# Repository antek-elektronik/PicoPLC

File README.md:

# picoPLC

Work in progress! 

This is 'industriual' adaptation for raspberry pi pico 2W. This is a hobby project developed by me (AntekElektronik) with no plans for building it (yet). 

## features 

This device features a 8 optotransistor 24V inputs, 4 10A 230V relay outputs and 4 transistor outputs latching to ground. The device is powered by 24V external power supply and has 24V -> 5V switching power regulator onboard (the rpi pico 2w takes care of regulating 3.3V). 

## wireles connectivity

I am aware that rpi pico's wireless features won't work enclosed inside a metal case. I plan on changing to esp32 with external antenna in future. This project could be used as a base for mainstream microcontroller based PLC controllers

## software

for the time of writing this, I do not have any software written. First stage would be a micropython file with predefined variables and functions for basic I/O operations on picoPLC platform, the rest would have to be written in micropython. 

I plan to use an existng project like openPLC, find something similar or write from scratch a program for executing ladder logic or function blocks.

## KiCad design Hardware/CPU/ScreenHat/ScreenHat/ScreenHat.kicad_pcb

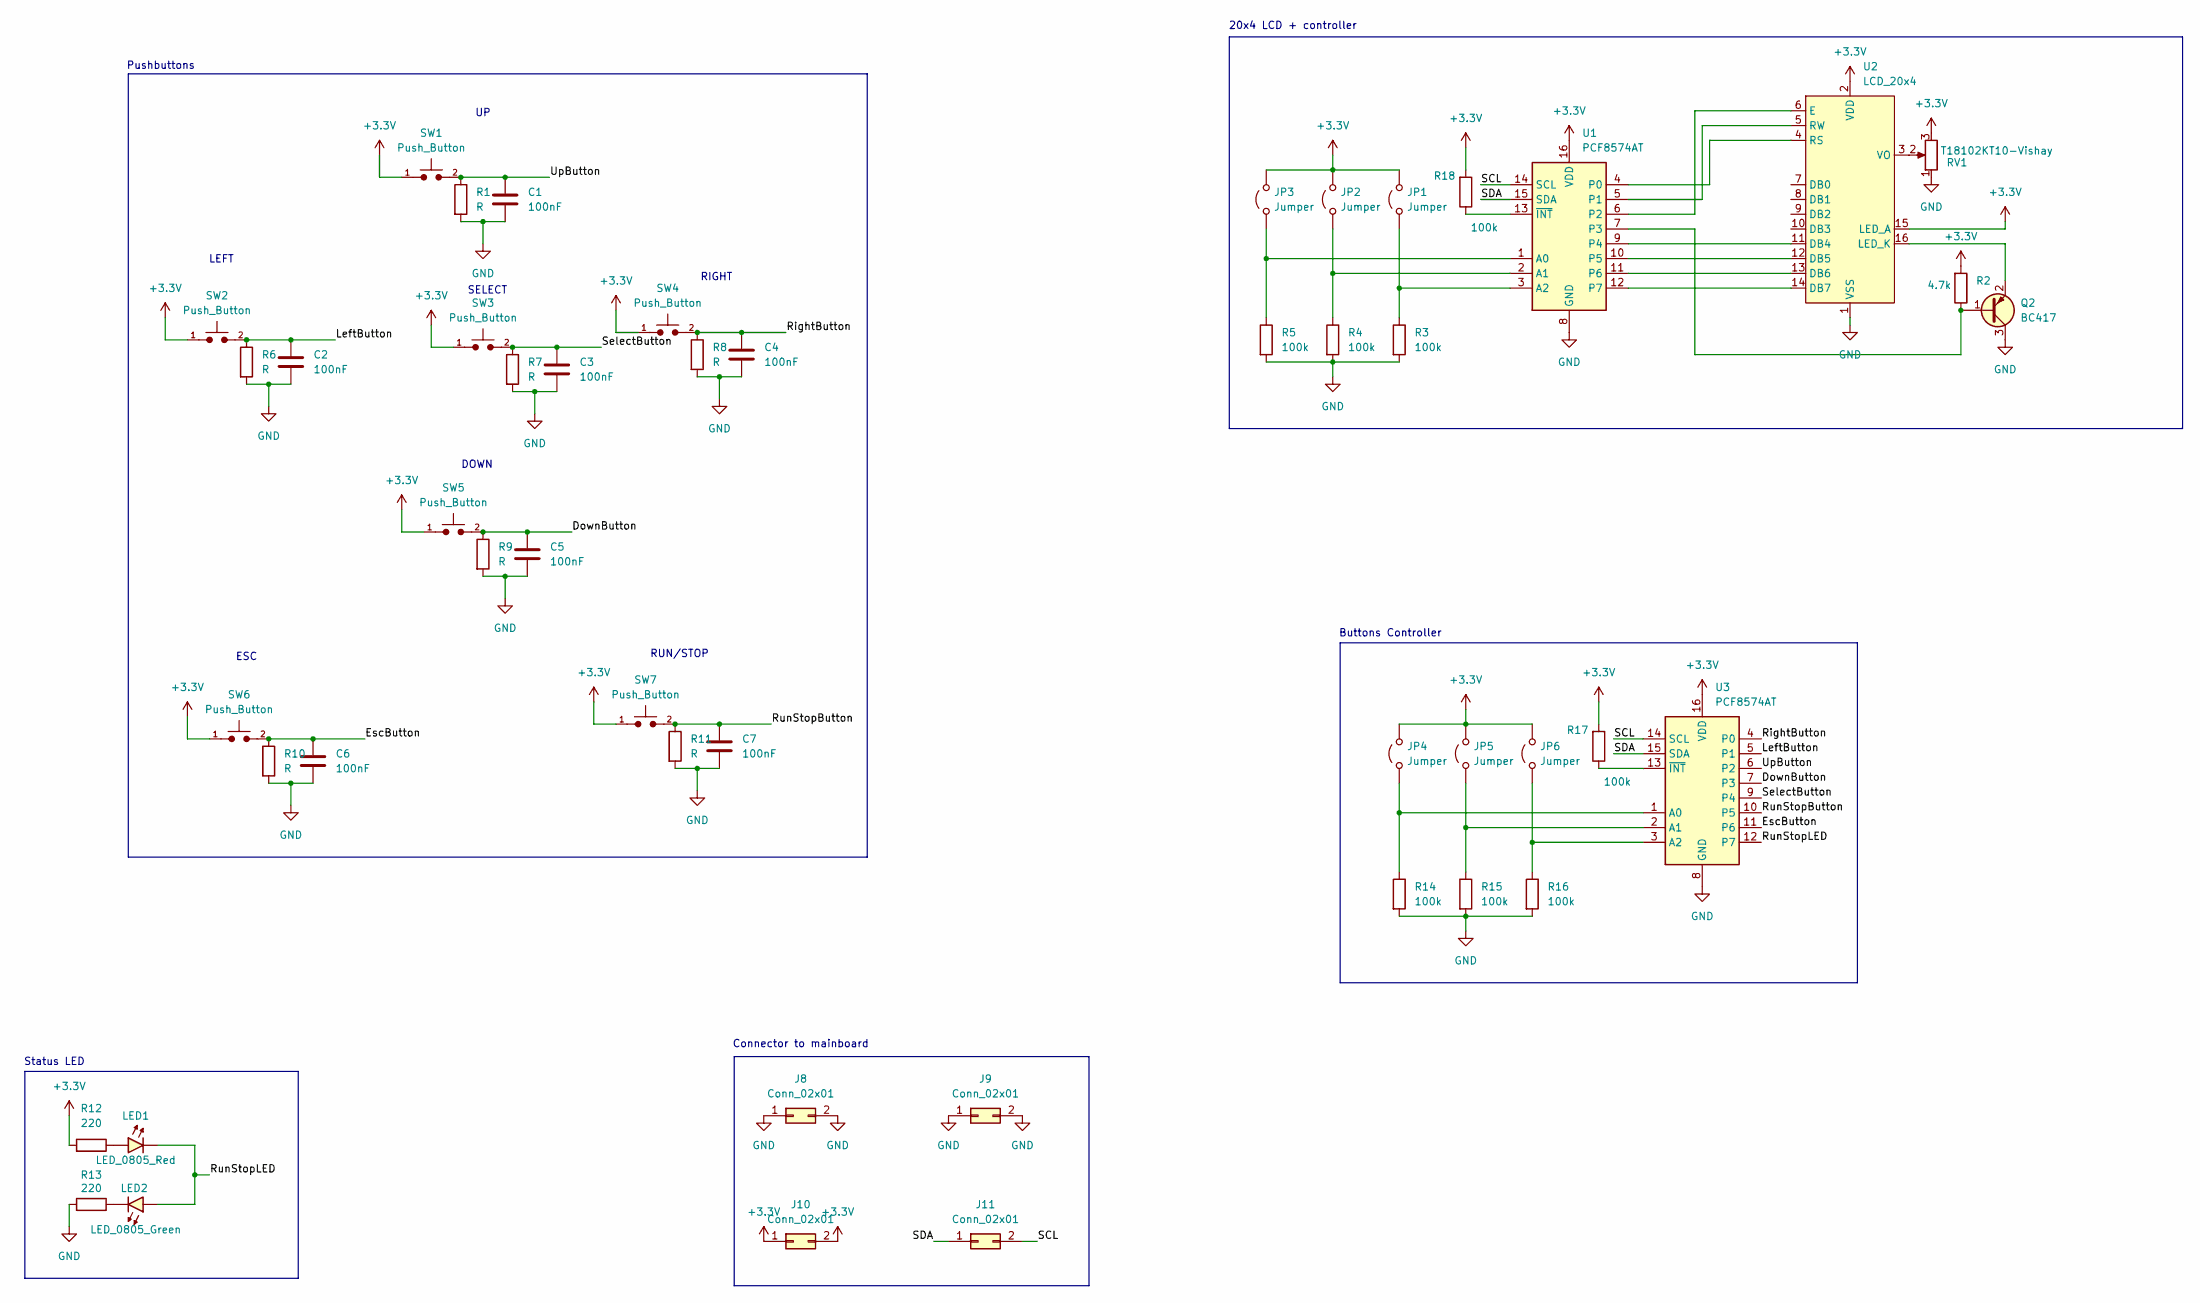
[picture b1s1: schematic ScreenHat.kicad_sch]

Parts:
C1, C2, C3, C4, C5, C6, C7: 100nF; C_0805_2012Metric_Pad1.18x1.45mm_HandSolder
J8, J9, J10, J11: Conn_02x01; PinHeader_2x01_P2.54mm_Vertical
JP1, JP2, JP3, JP4, JP5, JP6: Jumper; SolderJumper-2_P1.3mm_Open_RoundedPad1.0x1.5mm
LED1: LED_0805_Red; LED_0805_2012Metric
LED2: LED_0805_Green; LED_0805_2012Metric
Q2: BC417; SOT-23
R1, R6, R7, R8, R9, R10, R11: R; R_0805_2012Metric_Pad1.15x1.40mm_HandSolder
R2: 4.7k; R_0805_2012Metric
R3, R4, R5, R14, R15, R16: 100k; R_0805_2012Metric_Pad1.15x1.40mm_HandSolder
R12, R13: 220; R_0805_2012Metric
R17, R18: 100k; R_0805_2012Metric
RV1: T18102KT10-Vishay; Potentiometer_Bourns_3009P_Horizontal
SW1, SW2, SW3, SW4, SW5, SW6, SW7: Push_Button; SW_SPST_Omron_B3FS-105xP
U1, U3: PCF8574AT; SOIC-16W_7.5x10.3mm_P1.27mm
U2: LCD_20x4; LCD-16X4

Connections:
+3.3V: J10.1, J10.2, JP1.2 (B), JP2.2 (B), JP3.2 (B), JP4.2 (B), JP5.2 (B), JP6.2 (B), R2.1, R12.1, R17.1, R18.1, RV1.3, SW1.1, SW2.1, SW3.1, SW4.1, SW5.1, SW6.1, SW7.1, U1.16 (VDD), U2.2 (VDD), U2.15 (LED_A), U3.16 (VDD)
/DownButton: C5.1, R9.1, SW5.2, U3.7 (P3)
/EscButton: C6.1, R10.1, SW6.2, U3.11 (P6)
/LeftButton: C2.1, R6.1, SW2.2, U3.5 (P1)
/RightButton: C4.1, R8.1, SW4.2, U3.4 (P0)
/RunStopButton: C7.1, R11.1, SW7.2, U3.10 (P5)
/RunStopLED: LED1.1 (K), LED2.2 (A), U3.12 (P7)
/SCL: J11.2, U1.14 (SCL), U3.14 (SCL)
/SDA: J11.1, U1.15 (SDA), U3.15 (SDA)
/SelectButton: C3.1, R7.1, SW3.2, U3.9 (P4)
/UpButton: C1.1, R1.1, SW1.2, U3.6 (P2)
GND: C1.2, C2.2, C3.2, C4.2, C5.2, C6.2, C7.2, J8.1, J8.2, J9.1, J9.2, Q2.3 (C), R1.2, R3.2, R4.2, R5.2, R6.2, R7.2, R8.2, R9.2, R10.2, R11.2, R13.1, R14.2, R15.2, R16.2, RV1.1, U1.8 (GND), U2.1 (VSS), U3.8 (GND)
unnamed: JP1.1 (A), R3.1, U1.3 (A2)
unnamed: JP2.1 (A), R4.1, U1.2 (A1)
unnamed: JP3.1 (A), R5.1, U1.1 (A0)
unnamed: JP4.1 (A), R14.1, U3.1 (A0)
unnamed: JP5.1 (A), R15.1, U3.2 (A1)
unnamed: JP6.1 (A), R16.1, U3.3 (A2)
unnamed: LED1.2 (A), R12.2
unnamed: LED2.1 (K), R13.2
unnamed: Q2.1 (B), R2.2, U1.7 (P3)
unnamed: Q2.2 (E), U2.16 (LED_K)
unnamed: U1.4 (P0), U2.4 (RS)
unnamed: U1.5 (P1), U2.5 (RW)
unnamed: U1.6 (P2), U2.6 (E)
unnamed: U1.9 (P4), U2.11 (DB4)
unnamed: U1.10 (P5), U2.12 (DB5)
unnamed: U1.11 (P6), U2.13 (DB6)
unnamed: U1.12 (P7), U2.14 (DB7)
unnamed: R18.2, U1.13 (~INT)
unnamed: RV1.2, U2.3 (VO)
unnamed: R17.2, U3.13 (~INT)

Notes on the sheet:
DOWN
20x4 LCD + controller
ESC
RIGHT
Connector to mainboard
LEFT
Buttons Controller
SELECT
Pushbuttons
RUN/STOP
Status LED

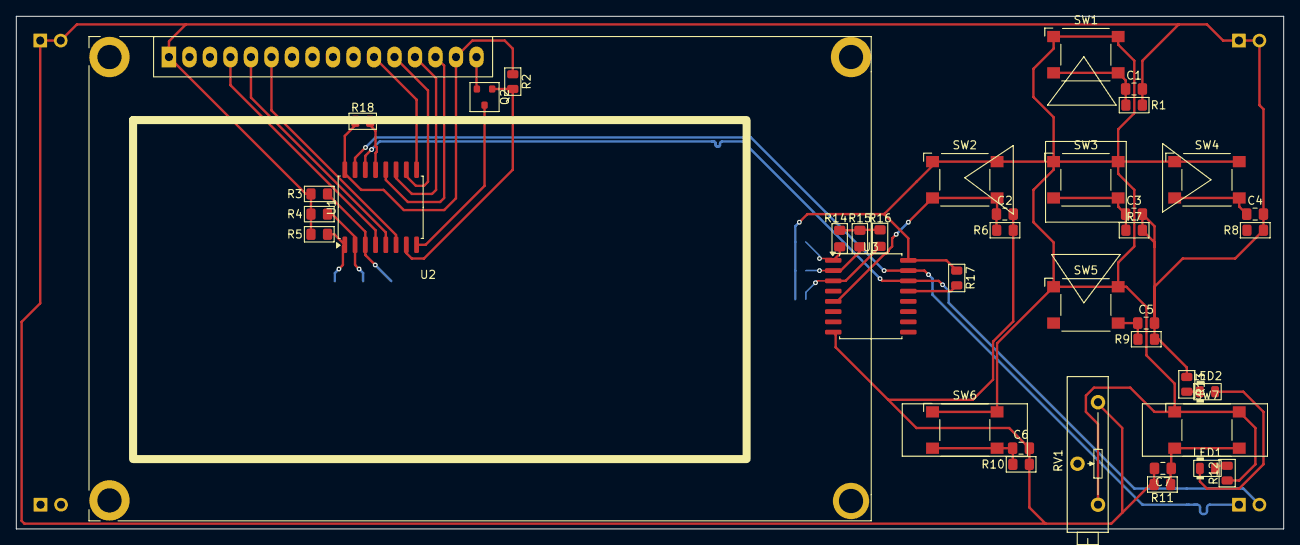
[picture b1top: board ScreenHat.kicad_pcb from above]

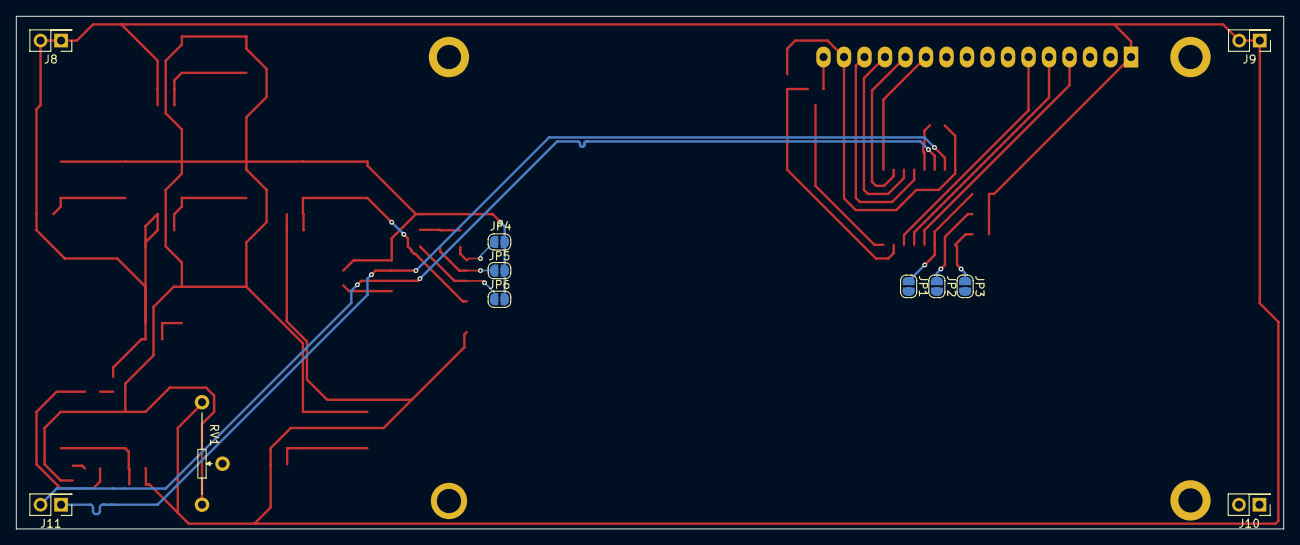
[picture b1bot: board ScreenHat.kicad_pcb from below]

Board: 2 copper layers, 157.0 x 63.5 mm, 49 parts (10 on the bottom side), 32 nets.

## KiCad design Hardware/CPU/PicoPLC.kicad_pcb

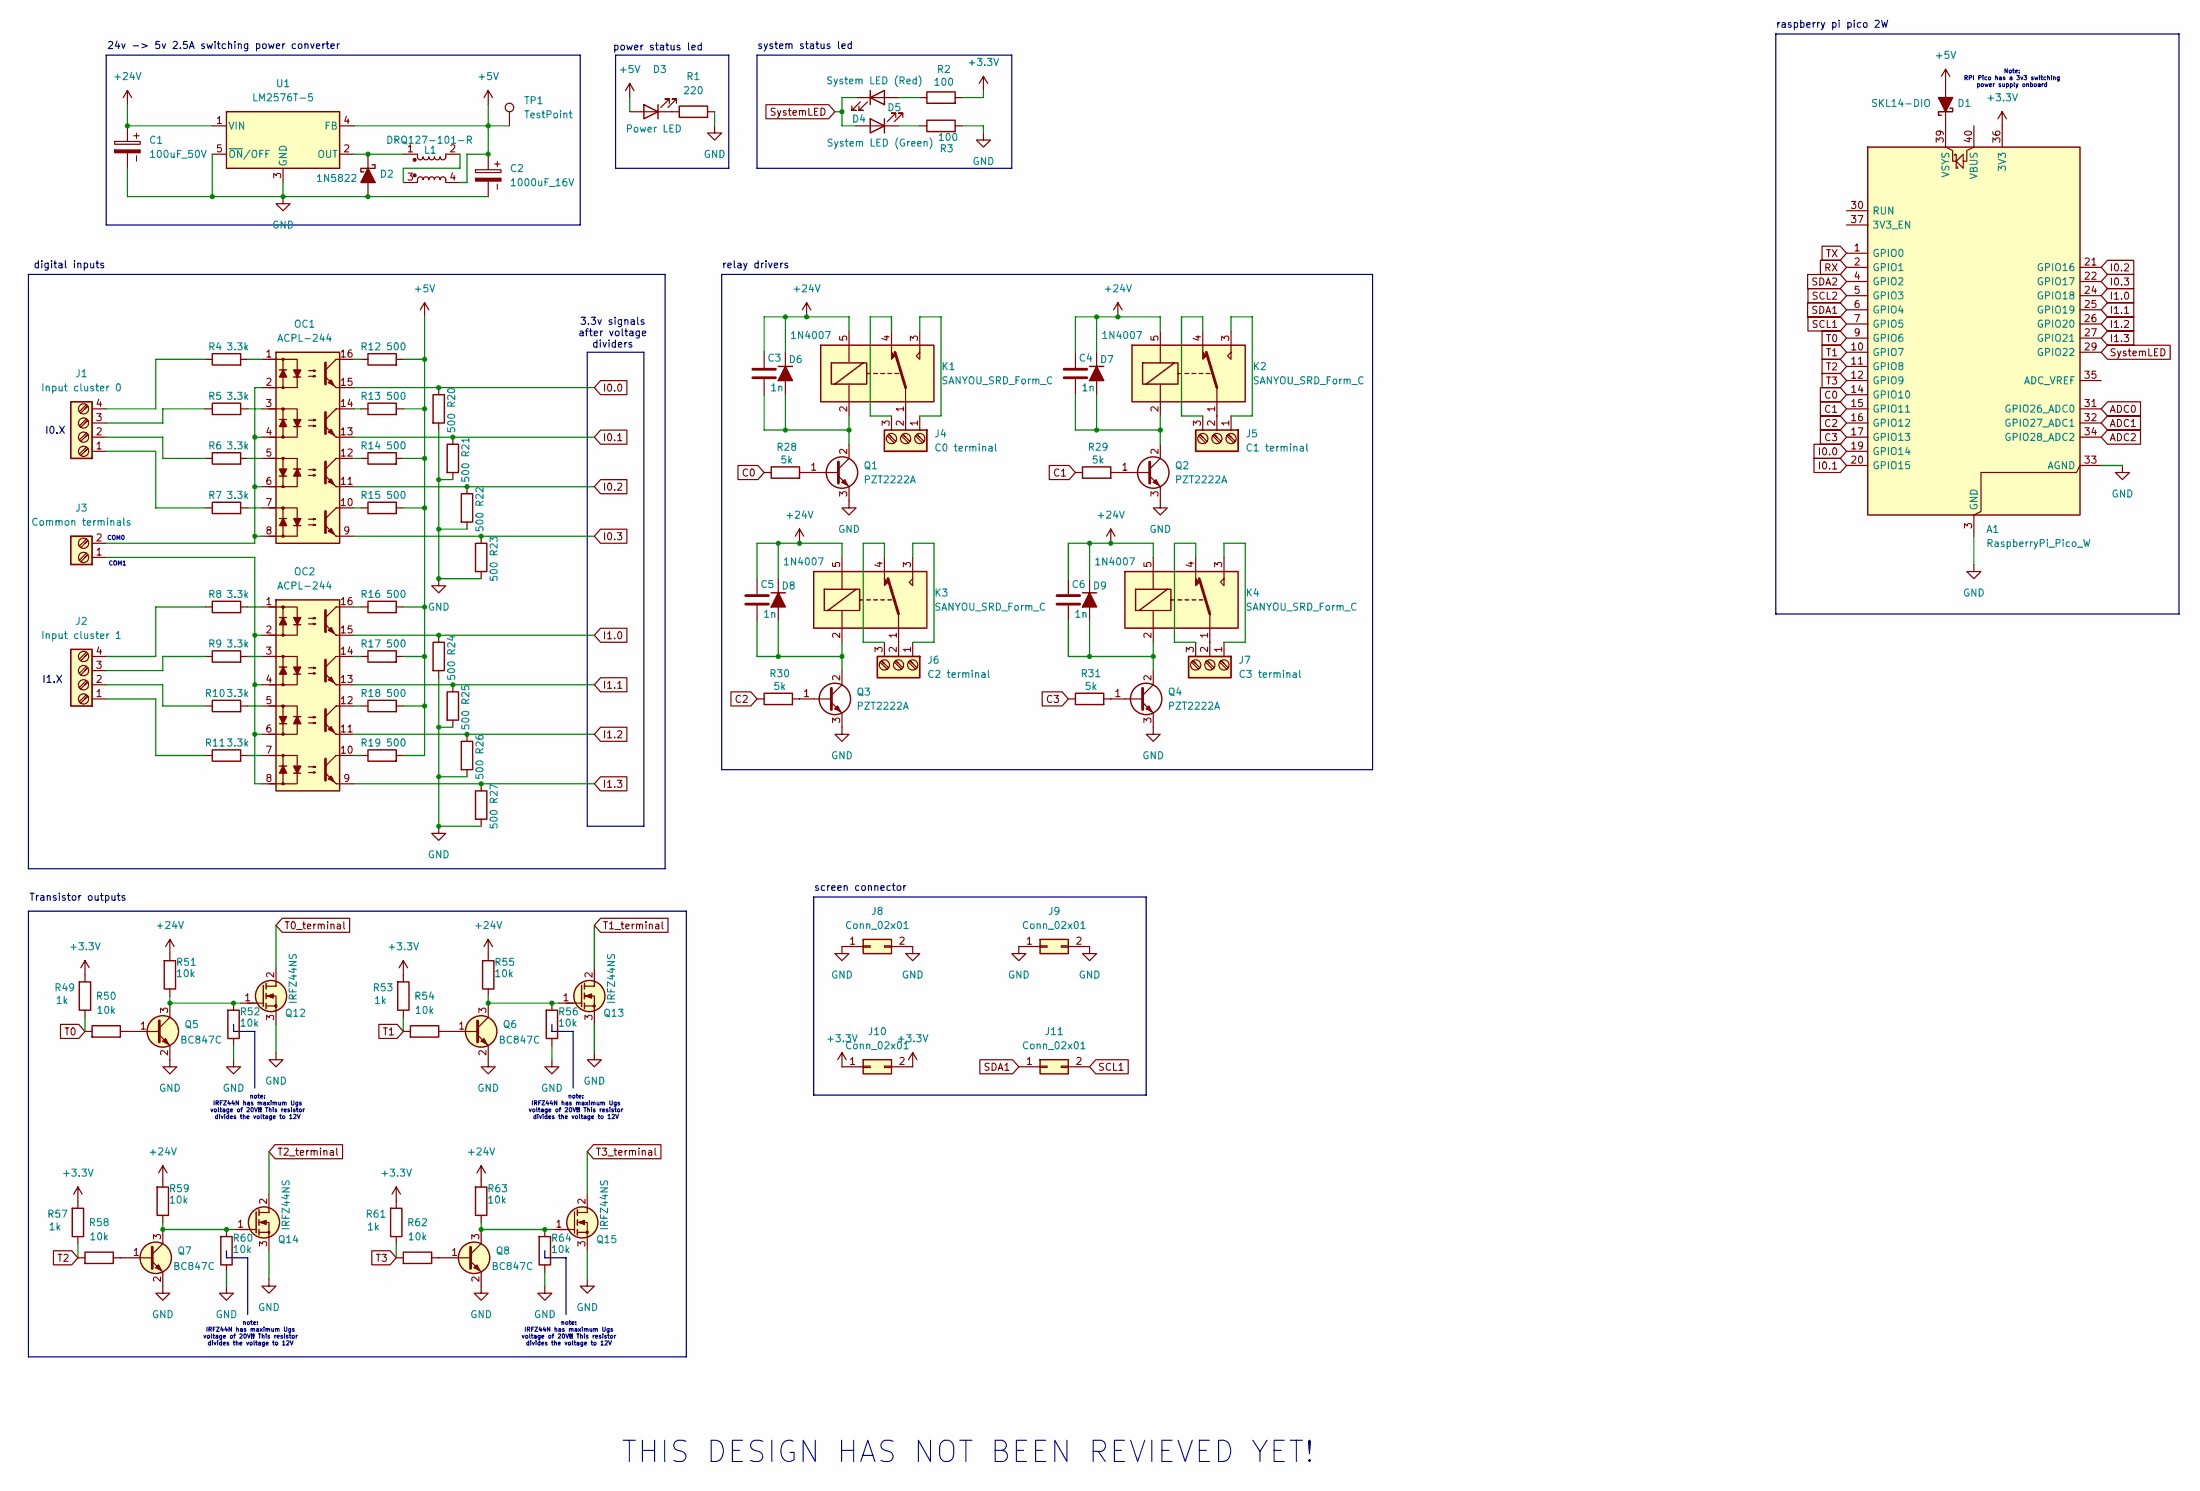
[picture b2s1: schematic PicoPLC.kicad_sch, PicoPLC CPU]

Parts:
A1: RaspberryPi_Pico_W; RaspberryPi_Pico_W_SMD_HandSolder
C1: 100uF_50V; CP_Radial_D8.0mm_P3.50mm
C2: 1000uF_16V; CP_Radial_D10.0mm_P5.00mm
C3, C4, C5, C6: 1n; C_0805_2012Metric_Pad1.18x1.45mm_HandSolder
D1: SKL14-DIO; D_SOD-123F
D2: 1N5822; D_DO-201AD_P12.70mm_Horizontal
D3: Power LED; LED_0805_2012Metric_Pad1.15x1.40mm_HandSolder
D4: System LED (Green); LED_0805_2012Metric_Pad1.15x1.40mm_HandSolder
D5: System LED (Red); LED_0805_2012Metric_Pad1.15x1.40mm_HandSolder
D6, D7, D8, D9: 1N4007; D_SOD-123
J1: Input cluster 0; TerminalBlock_Phoenix_PT-1,5-4-5.0-H_1x04_P5.00mm_Horizontal
J2: Input cluster 1; TerminalBlock_Phoenix_PT-1,5-4-5.0-H_1x04_P5.00mm_Horizontal
J3: Common terminals; TerminalBlock_Phoenix_PT-1,5-2-3.5-H_1x02_P3.50mm_Horizontal
J4: C0 terminal; TerminalBlock_Phoenix_PT-1,5-3-5.0-H_1x03_P5.00mm_Horizontal
J5: C1 terminal; TerminalBlock_Phoenix_PT-1,5-3-5.0-H_1x03_P5.00mm_Horizontal
J6: C2 terminal; TerminalBlock_Phoenix_PT-1,5-3-5.0-H_1x03_P5.00mm_Horizontal
J7: C3 terminal; TerminalBlock_Phoenix_PT-1,5-3-5.0-H_1x03_P5.00mm_Horizontal
J8: Conn_02x01; PinHeader_2x01_P2.54mm_Vertical
J9, J10, J11: Conn_02x01
K1, K2, K3, K4: SANYOU_SRD_Form_C; Relay_SPDT_SANYOU_SRD_Series_Form_C
L1: DRQ127-101-R; L_Bourns_SRF1260
OC1, OC2: ACPL-244; SO-16_5.3x10.2mm_P1.27mm
Q1, Q2, Q3, Q4: PZT2222A; SOT-223-3_TabPin2
Q5, Q6, Q7, Q8: BC847C; SOT-23
Q12, Q13, Q14, Q15: IRFZ44NS; TO-263-2
R1: 220; R_0805_2012Metric_Pad1.15x1.40mm_HandSolder
R2, R3: 100; R_0805_2012Metric_Pad1.15x1.40mm_HandSolder
R4, R5, R6, R7, R8, R9, R10, R11: 3.3k; R_0805_2012Metric_Pad1.15x1.40mm_HandSolder
R12, R13, R14, R15, R16, R17, R18, R19, R20, R21, R22, R23, R24, R25, R26, R27: 500; R_0805_2012Metric_Pad1.15x1.40mm_HandSolder
R28, R29, R30, R31: 5k; R_0805_2012Metric_Pad1.15x1.40mm_HandSolder
R49, R53, R57, R61: 1k; R_1806_4516Metric
R50, R51, R52, R54, R55, R56, R58, R59, R60, R62, R63, R64: 10k; R_1806_4516Metric
TP1: TestPoint; TestPoint_Pad_D2.0mm
U1: LM2576T-5; TO-220-5_Horizontal_TabDown

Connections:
+3.3V: A1.36 (3V3), J10.1, J10.2, R2.2, R49.1, R53.1, R57.1, R61.1
+5V: C2.1, D1.2 (A), D3.2 (A), L1.4, R12.2, R13.2, R14.2, R15.2, R16.2, R17.2, R18.2, R19.2, TP1.1, U1.4 (FB)
+24V: C1.1, C3.1, C4.1, C5.1, C6.1, D6.1 (K), D7.1 (K), D8.1 (K), D9.1 (K), K1.5, K2.5, K3.5, K4.5, R51.1, R55.1, R59.1, R63.1, U1.1 (VIN)
ADC0: A1.31 (GPIO26_ADC0)
ADC1: A1.32 (GPIO27_ADC1)
ADC2: A1.34 (GPIO28_ADC2)
C0: A1.14 (GPIO10), R28.1
C1: A1.15 (GPIO11), R29.1
C2: A1.16 (GPIO12), R30.1
C3: A1.17 (GPIO13), R31.1
GND: A1.3 (GND), A1.8 (GND), A1.13 (GND), A1.18 (GND), A1.23 (GND), A1.28 (GND), A1.33 (AGND), A1.38 (GND), C1.2, C2.2, D2.2 (A), J8.1, J8.2, J9.1, J9.2, Q1.3 (E), Q2.3 (E), Q3.3 (E), Q4.3 (E), Q5.2 (E), Q6.2 (E), Q7.2 (E), Q8.2 (E), Q12.3 (S), Q13.3 (S), Q14.3 (S), Q15.3 (S), R1.2, R3.2, R20.2, R21.2, R22.2, R23.2, R24.2, R25.2, R26.2, R27.2, R52.2, R56.2, R60.2, R64.2, U1.3 (GND), U1.5 (~ON/OFF)
I0.0: A1.19 (GPIO14), OC1.15, R20.1
I0.1: A1.20 (GPIO15), OC1.13, R21.1
I0.2: A1.21 (GPIO16), OC1.11, R22.1
I0.3: A1.22 (GPIO17), OC1.9, R23.1
I1.0: A1.24 (GPIO18), OC2.15, R24.1
I1.1: A1.25 (GPIO19), OC2.13, R25.1
I1.2: A1.26 (GPIO20), OC2.11, R26.1
I1.3: A1.27 (GPIO21), OC2.9, R27.1
unnamed: A1.39 (VSYS), D1.1 (K)
unnamed: D2.1 (K), L1.1, U1.2 (OUT)
unnamed: D3.1 (K), R1.1
unnamed: D4.1 (K), R3.1
unnamed: D5.2 (A), R2.1
unnamed: C3.2, D6.2 (A), K1.2, Q1.2 (C)
unnamed: C4.2, D7.2 (A), K2.2, Q2.2 (C)
unnamed: C5.2, D8.2 (A), K3.2, Q3.2 (C)
unnamed: C6.2, D9.2 (A), K4.2, Q4.2 (C)
unnamed: J1.1, R7.1
unnamed: J1.2, R6.1
unnamed: J1.3, R5.1
unnamed: J1.4, R4.1
unnamed: J2.1, R11.1
unnamed: J2.2, R10.1
unnamed: J2.3, R9.1
unnamed: J2.4, R8.1
unnamed: J3.1, OC2.2, OC2.4, OC2.6, OC2.8
unnamed: J3.2, OC1.2, OC1.4, OC1.6, OC1.8
unnamed: J4.1, K1.3
unnamed: J4.2, K1.1
unnamed: J4.3, K1.4
unnamed: J5.1, K2.3
unnamed: J5.2, K2.1
unnamed: J5.3, K2.4
unnamed: J6.1, K3.3
unnamed: J6.2, K3.1
unnamed: J6.3, K3.4
unnamed: J7.1, K4.3
unnamed: J7.2, K4.1
unnamed: J7.3, K4.4
unnamed: L1.2, L1.3
unnamed: OC1.1, R4.2
unnamed: OC1.3, R5.2
unnamed: OC1.5, R6.2
unnamed: OC1.7, R7.2
unnamed: OC1.10, R15.1
unnamed: OC1.12, R14.1
unnamed: OC1.14, R13.1
unnamed: OC1.16, R12.1
unnamed: OC2.1, R8.2
unnamed: OC2.3, R9.2
unnamed: OC2.5, R10.2
unnamed: OC2.7, R11.2
unnamed: OC2.10, R19.1
unnamed: OC2.12, R18.1
unnamed: OC2.14, R17.1
unnamed: OC2.16, R16.1
unnamed: Q1.1 (B), R28.2
unnamed: Q2.1 (B), R29.2
unnamed: Q3.1 (B), R30.2
unnamed: Q4.1 (B), R31.2
unnamed: Q5.1 (B), R50.2
unnamed: Q6.1 (B), R54.2
unnamed: Q7.1 (B), R58.2
unnamed: Q8.1 (B), R62.2
unnamed: Q5.3 (C), Q12.1 (G), R51.2, R52.1
unnamed: Q6.3 (C), Q13.1 (G), R55.2, R56.1
unnamed: Q7.3 (C), Q14.1 (G), R59.2, R60.1
unnamed: Q8.3 (C), Q15.1 (G), R63.2, R64.1
RX: A1.2 (GPIO1)
SCL1: A1.7 (GPIO5), J11.2
SCL2: A1.5 (GPIO3)
SDA1: A1.6 (GPIO4), J11.1
SDA2: A1.4 (GPIO2)
SystemLED: A1.29 (GPIO22), D4.2 (A), D5.1 (K)
T0: A1.9 (GPIO6), R49.2, R50.1
T0_terminal: Q12.2 (D)
T1: A1.10 (GPIO7), R53.2, R54.1
T1_terminal: Q13.2 (D)
T2: A1.11 (GPIO8), R57.2, R58.1
T2_terminal: Q14.2 (D)
T3: A1.12 (GPIO9), R61.2, R62.1
T3_terminal: Q15.2 (D)
TX: A1.1 (GPIO0)

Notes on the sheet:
Transistor outputs
relay drivers
note: IRFZ44N has maximum Ugs voltage of 20V!! This resistor divides the voltage to 12V
3.3v signals after voltage dividers
digital inputs
24v -> 5v 2.5A switching power converter
I1.X
I0.X
COM1
screen connector
system status led
COM0
THIS DESIGN HAS NOT BEEN REVIEVED YET!
power status led
raspberry pi pico 2W
Note: RPI Pico has a 3v3 switching power supply onboard

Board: 2 copper layers, 92 parts (0 on the bottom side), 81 nets, no tracks yet.

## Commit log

2025-05-20 added files
    added files
2025-06-27 working on screen capabilities
2025-08-11 finished ScreenHat Schematics
2025-08-11 started designing ScreenHat Board
